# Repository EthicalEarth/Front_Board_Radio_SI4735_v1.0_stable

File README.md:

# Front_Board_Radio_SI4735_v1.0_stable

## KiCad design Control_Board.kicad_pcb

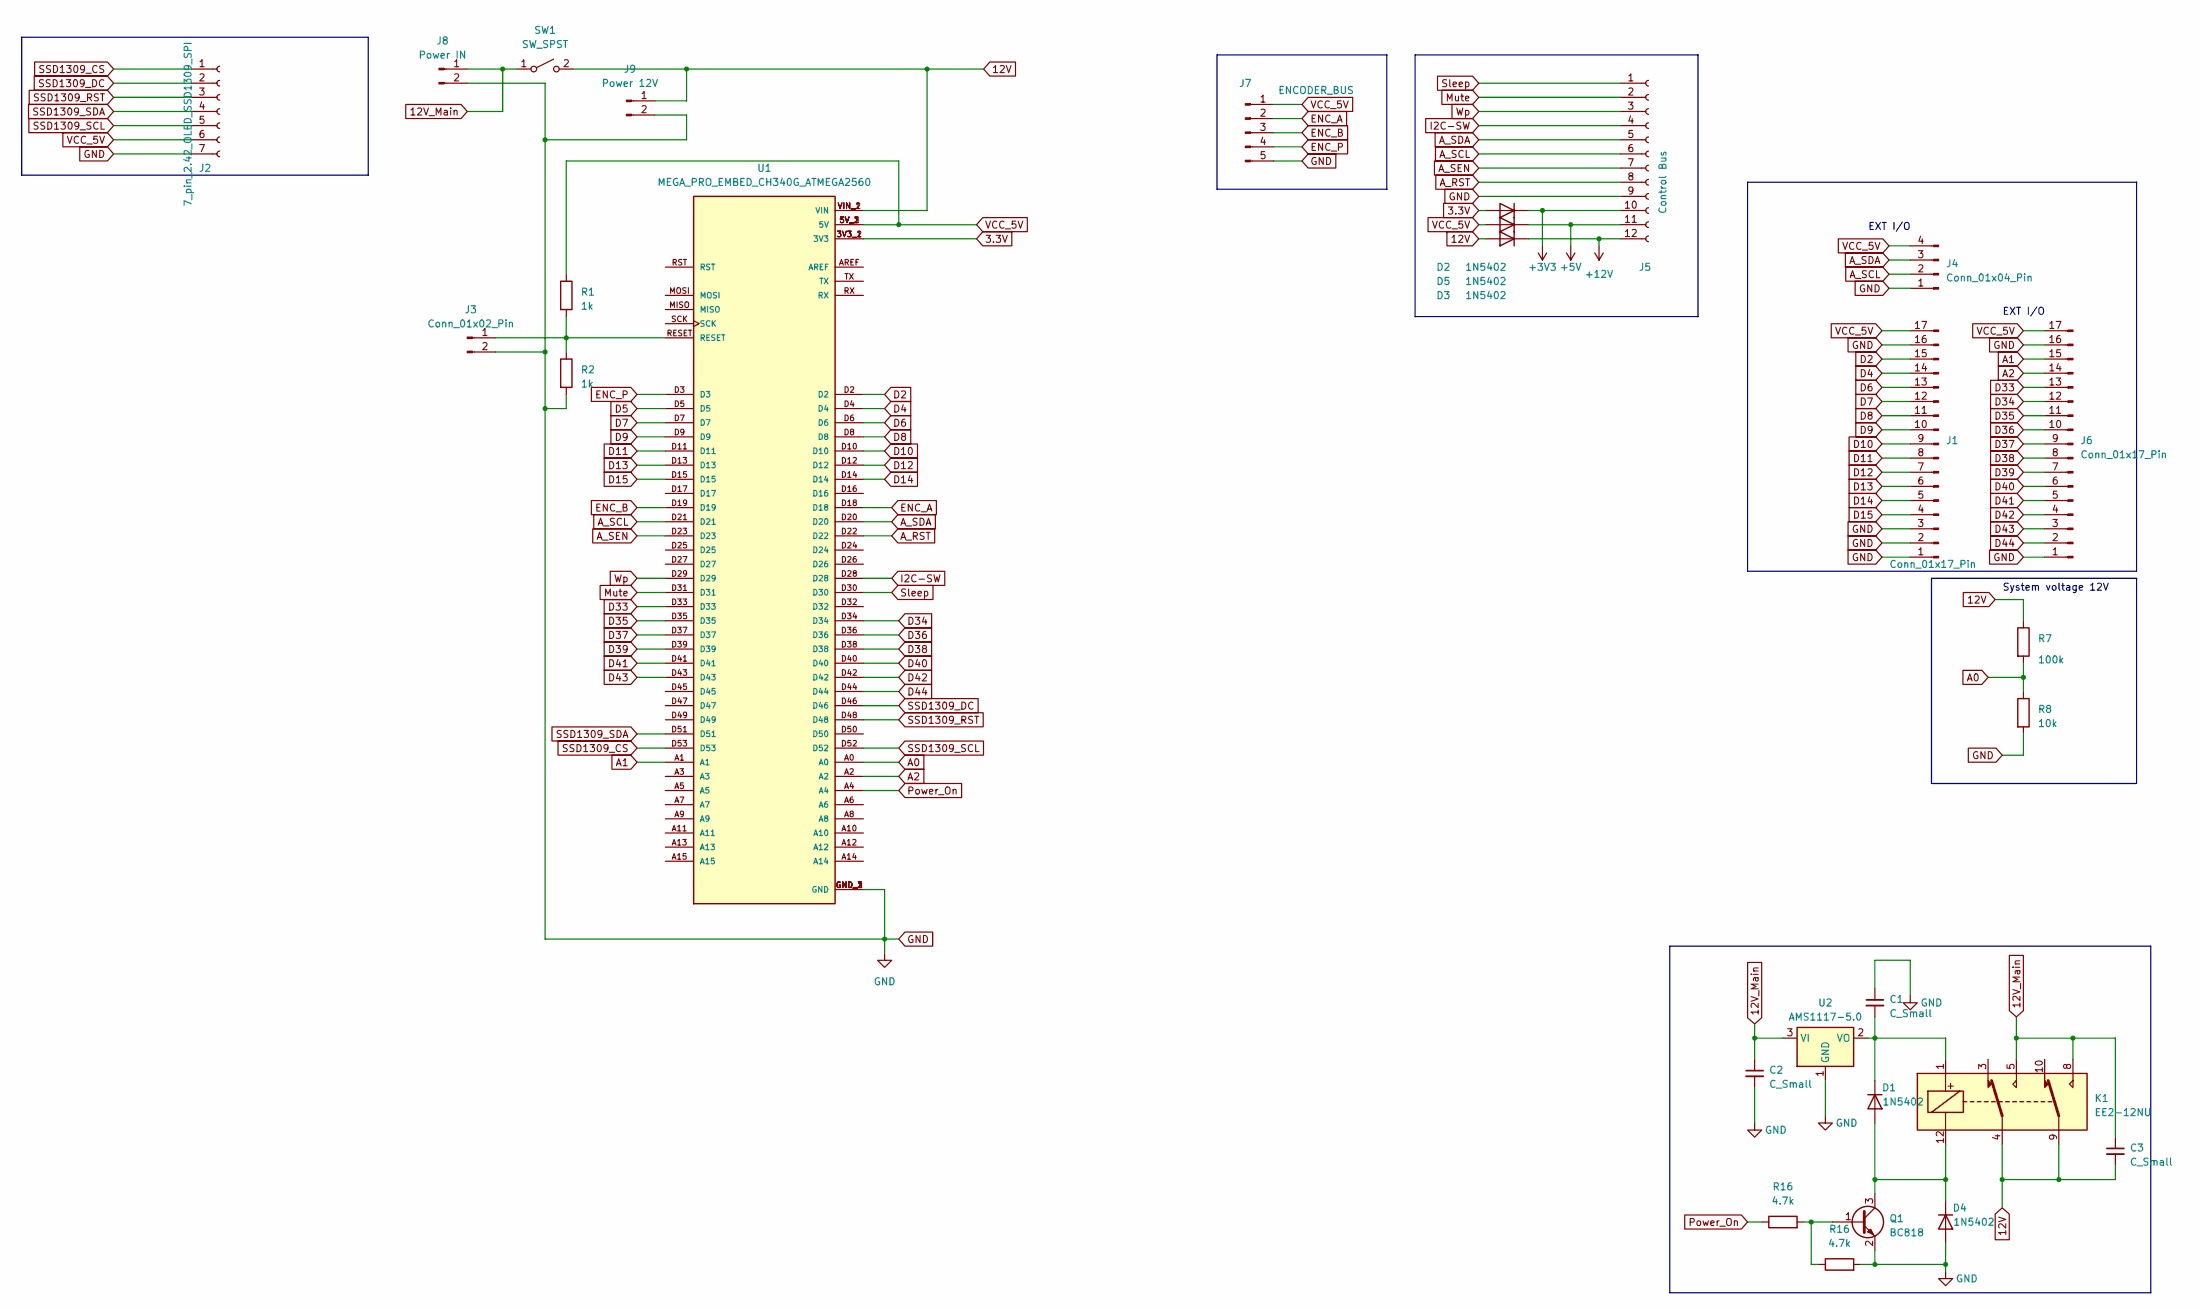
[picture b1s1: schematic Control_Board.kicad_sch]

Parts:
C1, C2, C3: C_Small; C_1206_3216Metric_Pad1.33x1.80mm_HandSolder
D1, D2, D3, D4, D5: 1N5402; D_1206_3216Metric
J1, J6: Conn_01x17_Pin; PinHeader_1x17_P2.54mm_Vertical
J2: 7_pin_2.42_OLED_SSD1309_SPI; PinSocket_1x07_P2.54mm_Vertical
J3: Conn_01x02_Pin; PinHeader_1x02_P1.27mm_Vertical
J4: Conn_01x04_Pin; PinHeader_1x04_P2.54mm_Vertical
J5: Control Bus; PinSocket_1x12_P2.54mm_Vertical
J7: ENCODER_BUS; PinHeader_1x05_P2.54mm_Vertical
J8: Power IN; PinSocket_1x02_P2.54mm_Vertical
J9: Power 12V; PinSocket_1x02_P2.54mm_Vertical
K1: EE2-12NU; Relay_DPDT_Kemet_EE2_NU
Q1: BC818; SOT-23
R1, R2: 1k; R_1206_3216Metric
R7: 100k; R_1206_3216Metric
R8: 10k; R_1206_3216Metric
R16: 4.7k; R_1206_3216Metric
SW1: SW_SPST; PinSocket_1x02_P2.54mm_Vertical
U1: MEGA_PRO_EMBED_CH340G_ATMEGA2560; MODULE_MEGA_PRO_EMBED_CH340G_ATMEGA2560; PARTREV 12/May/2017
U2: AMS1117-5.0; SOT-223-3_TabPin2

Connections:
3.3V: D2.2 (A), U1.3V3_1 (3V3), U1.3V3_2 (3V3)
12V: C3.2, D5.2 (A), J9.1, K1.4, K1.9, R7.1, SW1.2 (B), U1.VIN_1 (VIN), U1.VIN_2 (VIN)
12V_Main: C2.1, C3.1, J8.1, K1.5, K1.8, SW1.1 (A), U2.3 (VI)
+3V3: D2.1 (K), J5.10
+5V: D3.1 (K), J5.11
+12V: D5.1 (K), J5.12
A0: R7.2, R8.1, U1.A0
A1: J6.15, U1.A1
A2: J6.14, U1.A2
A_RST: J5.8, U1.D22
A_SCL: J4.2, J5.6, U1.D21
A_SDA: J4.3, J5.5, U1.D20
A_SEN: J5.7, U1.D23
D2: J1.15, U1.D2
D4: J1.14, U1.D4
D5: U1.D5
D6: J1.13, U1.D6
D7: J1.12, U1.D7
D8: J1.11, U1.D8
D9: J1.10, U1.D9
D10: J1.9, U1.D10
D11: J1.8, U1.D11
D12: J1.7, U1.D12
D13: J1.6, U1.D13
D14: J1.5, U1.D14
D15: J1.4, U1.D15
D33: J6.13, U1.D33
D34: J6.12, U1.D34
D35: J6.11, U1.D35
D36: J6.10, U1.D36
D37: J6.9, U1.D37
D38: J6.8, U1.D38
D39: J6.7, U1.D39
D40: J6.6, U1.D40
D41: J6.5, U1.D41
D42: J6.4, U1.D42
D43: J6.3, U1.D43
D44: J6.2, U1.D44
ENC_A: J7.2, U1.D18
ENC_B: J7.3, U1.D19
ENC_P: J7.4, U1.D3
GND: C1.1, C2.2, D4.2 (A), J1.1, J1.2, J1.3, J1.16, J2.7, J3.2, J4.1, J5.9, J6.1, J6.16, J7.5, J8.2, J9.2, Q1.2 (E), R2.2, R8.2, U1.GND_1 (GND), U1.GND_2 (GND), U1.GND_3 (GND), U2.1 (GND); also elsewhere on the board
I2C-SW: J5.4, U1.D28
Mute: J5.2, U1.D31
unnamed: D1.2 (A), D4.1 (K), K1.12, Q1.3 (C)
unnamed: C1.2, D1.1 (K), K1.1, U2.2 (VO)
unnamed: J3.1, R1.2, R2.1, U1.RESET
unnamed 47: Q1.1 (B); also elsewhere on the board
Power_On: U1.A4; also elsewhere on the board
SSD1309_CS: J2.1, U1.D53
SSD1309_DC: J2.2, U1.D46
SSD1309_RST: J2.3, U1.D48
SSD1309_SCL: J2.5, U1.D52
SSD1309_SDA: J2.4, U1.D51
Sleep: J5.1, U1.D30
VCC_5V: D3.2 (A), J1.17, J2.6, J4.4, J6.17, J7.1, R1.1, U1.5V_1 (5V), U1.5V_2 (5V), U1.5V_3 (5V)
Wp: J5.3, U1.D29

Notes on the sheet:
System voltage 12V
EXT I/O

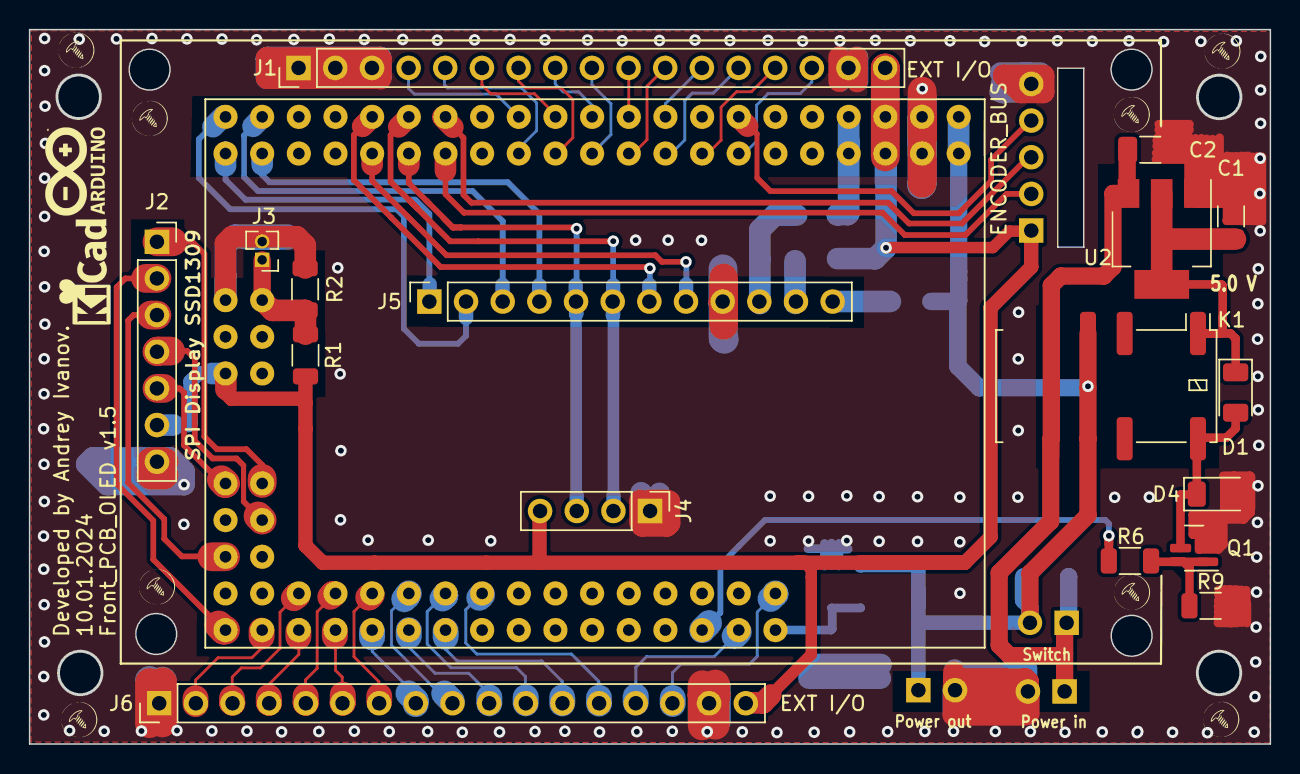
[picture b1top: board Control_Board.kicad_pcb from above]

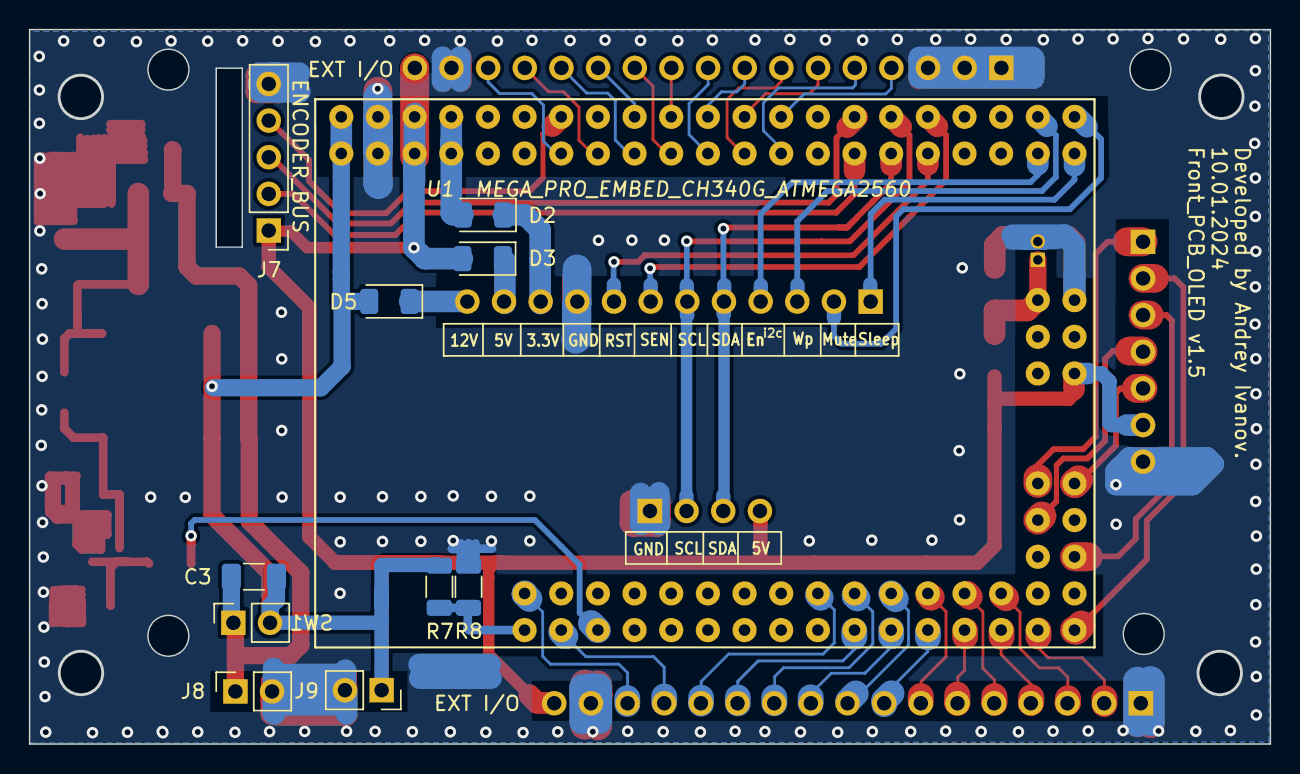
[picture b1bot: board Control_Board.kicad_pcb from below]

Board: 2 copper layers, 86.0 x 49.5 mm, 28 parts (10 on the bottom side), 56 nets.

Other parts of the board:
R6, R9: 4.7k; R_1206_3216Metric

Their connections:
GND: R9.2; also elsewhere on the board
unnamed 47: R6.2, R9.1; also elsewhere on the board
Power_On: R6.1; also elsewhere on the board
